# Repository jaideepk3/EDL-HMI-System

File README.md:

# HMI System for Corrosion Monitoring Product WEL-iPEC

This repository contains the development files for a Human Machine Interface (HMI) system designed for use with a corrosion monitoring product (iPEC-Probe). The HMI system includes a user interface with buttons connected to a microcontroller. Due to the unavailability of direct connection with the iPEC Probe, various sensors have been used to simulate data that will be displayed on the LCD screen.

## Files

The repository consists of the following files:

- **Packaging Enclosure CAD**: This folder contains CAD files for the packaging enclosure of the HMI system.

- **Board Files**: This folder contains the PCB design files for the microcontroller board.

- **HMI Code**: This folder contains the complex code that runs the HMI system.

- **Project Report**: This file is a comprehensive documented report of the entire project. It provides detailed information about the development process, implementation, and results. [Download Project Report](https://github.com/jaideepk3/EDL-HMI-System/blob/main/TUES-25_final_report.pdf)

## Project Description

### Aim
The aim of this project is to develop an HMI system that interfaces with the iPEC-Probe corrosion monitoring product. The HMI system will provide a user interface with buttons connected to a microcontroller. To simulate real-time data, sensors have been utilized instead of the actual iPEC Probe.

### Description
The project utilizes a Raspberry Pi Pico microcontroller board as the central controller for the HMI system. The microcontroller board interfaces with various buttons and an LCD screen. The buttons enable user interaction with the LCD screen, while the microcontroller controls the display based on the button inputs.

The HMI system displays real-time measurements obtained from various sensors, including the distance traveled from the scanning start point, rebar depth, rebar size, and other parameters. This provides users with an overview of the concrete structure's condition, enabling informed decision-making. The simulated values from the sensors facilitate comprehensive testing of the HMI system.

## Getting Started

To get started with the HMI system development, follow these steps:

1. Clone this repository to your local machine.
2. Navigate to the respective folders to access the CAD files, board design files, and HMI code.
3. Refer to the documentation provided in the report for further instructions.

## Additional Resources

- **Demo Video**: Watch a breadboard circuit demonstration of the HMI system in action. [Watch Demo Video](https://drive.google.com/file/d/1d6G7GhgJb7exQOc0swpD6kvzHQxaDGIW/view?usp=drivesdk)

- **Final Presentation**: Access the final presentation video for a detailed overview of the project. [View Final Presentation](https://drive.google.com/file/d/1m0dKYORe6IZ8-cWrcGXbmrLrGEMQUf9Z/view?usp=share_link)

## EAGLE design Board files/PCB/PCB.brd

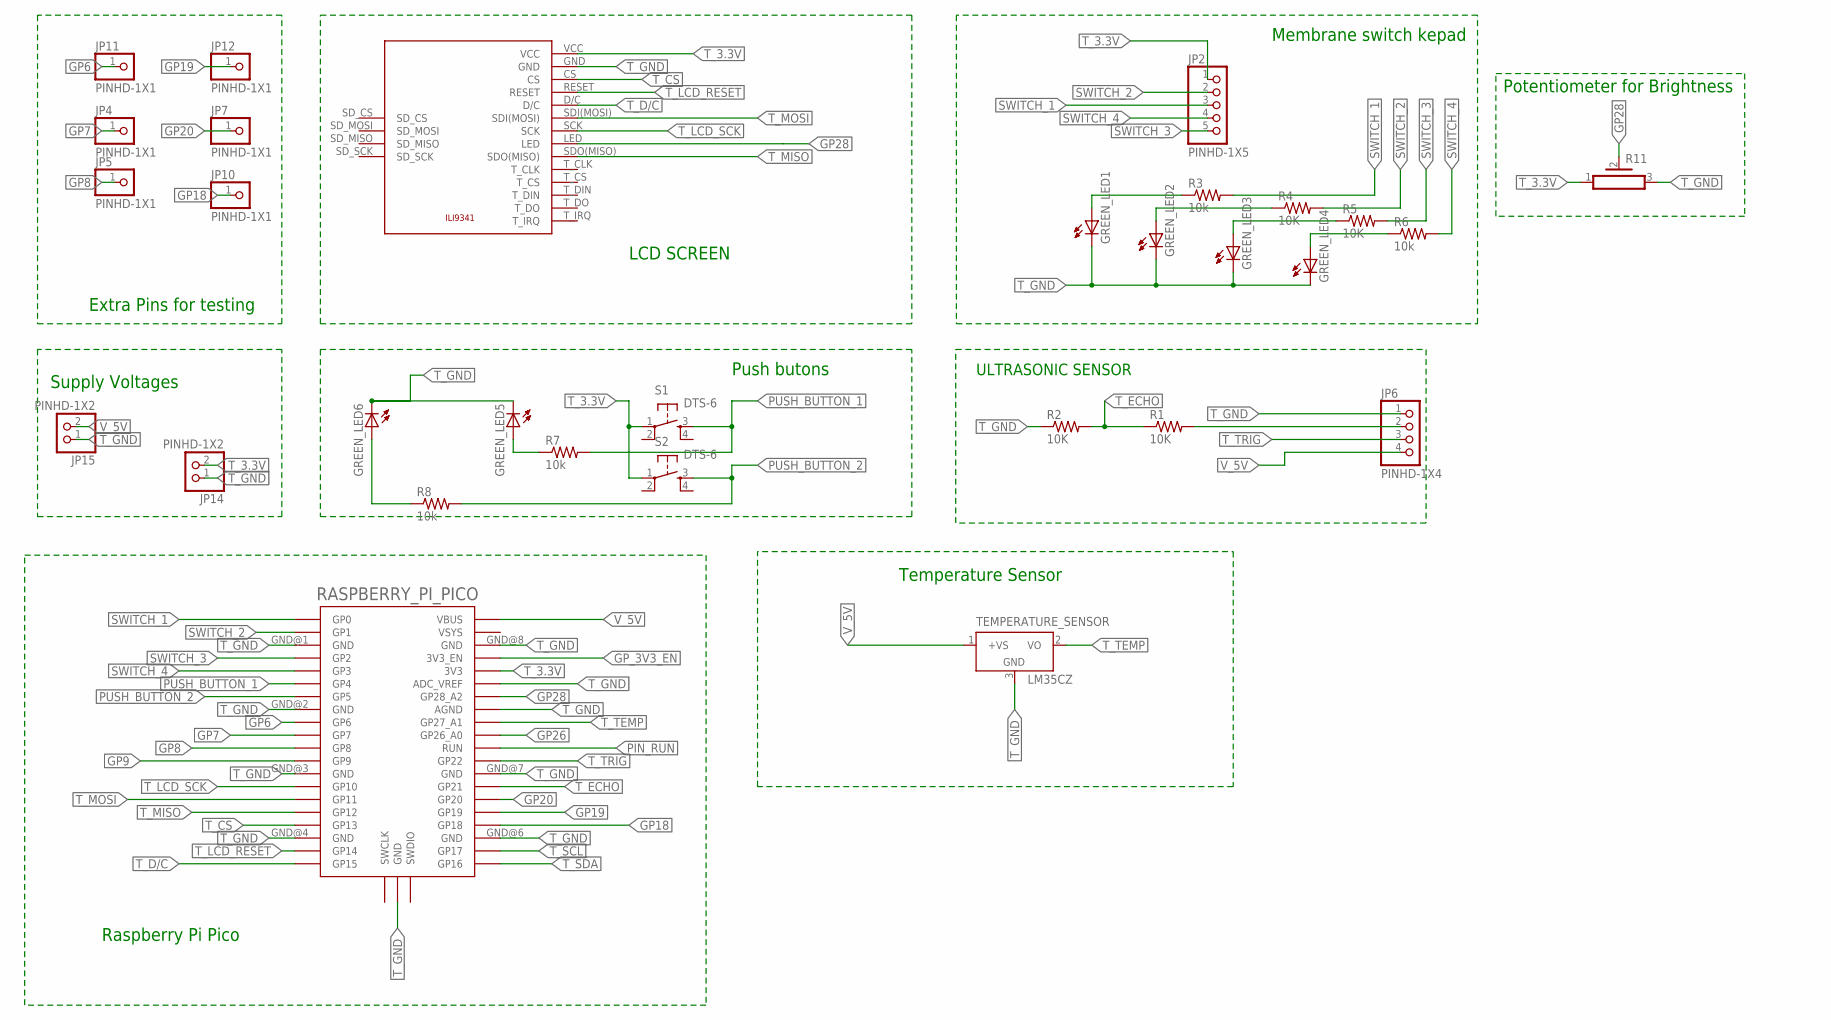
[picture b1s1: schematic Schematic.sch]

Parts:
GREEN_LED1, GREEN_LED2, GREEN_LED3, GREEN_LED4, GREEN_LED5, GREEN_LED6: 3MM_LED_TH; LED3MM
JP2: PINHD-1X5; 1X05
JP4, JP5, JP7, JP10, JP11, JP12: PINHD-1X1; 1X01
JP6: PINHD-1X4; 1X04
JP14, JP15: PINHD-1X2; 1X02
LCD_SCREEN: ILI9341
R1, R2, R4, R5: 10K; 0207/10
R3, R6, R7, R8: 10k; 0207/10
R11: PV36Y
RASPBERRY_PI_PICO: RPI_PICO_IG-TH; RPI_PICO_TH
S1, S2: DTS-6
TEMPERATURE_SENSOR: LM35CZ; TO92

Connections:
GP6: JP11.1, RASPBERRY_PI_PICO.GP6
GP7: JP4.1, RASPBERRY_PI_PICO.GP7
GP8: JP5.1, RASPBERRY_PI_PICO.GP8
GP9: RASPBERRY_PI_PICO.GP9
GP18: JP10.1, RASPBERRY_PI_PICO.GP18
GP19: JP12.1, RASPBERRY_PI_PICO.GP19
GP20: JP7.1, RASPBERRY_PI_PICO.GP20
GP26: RASPBERRY_PI_PICO.GP26_A0
GP28: LCD_SCREEN.LED, R11.2, RASPBERRY_PI_PICO.GP28_A2
GP_3V3_EN: RASPBERRY_PI_PICO.3V3_EN
unnamed: JP6.2, R1.2
unnamed: GREEN_LED4.A, R6.1
unnamed: GREEN_LED3.A, R5.1
unnamed: GREEN_LED2.A, R4.1
unnamed: GREEN_LED1.A, R3.1
unnamed: GREEN_LED5.A, R7.1
unnamed: GREEN_LED6.A, R8.1
PIN_RUN: RASPBERRY_PI_PICO.RUN
PUSH_BUTTON_1: R7.2, RASPBERRY_PI_PICO.GP4, S1.3
PUSH_BUTTON_2: R8.2, RASPBERRY_PI_PICO.GP5, S2.3
SWITCH_1: JP2.3, R3.2, RASPBERRY_PI_PICO.GP0
SWITCH_2: JP2.2, R4.2, RASPBERRY_PI_PICO.GP1
SWITCH_3: JP2.5, R5.2, RASPBERRY_PI_PICO.GP2
SWITCH_4: JP2.4, R6.2, RASPBERRY_PI_PICO.GP3
T_3.3V: JP2.1, JP14.2, LCD_SCREEN.VCC, R11.1, RASPBERRY_PI_PICO.3V3, S1.1, S2.1
T_CS: LCD_SCREEN.CS, RASPBERRY_PI_PICO.GP13
T_D/C: LCD_SCREEN.D/C, RASPBERRY_PI_PICO.GP15
T_ECHO: R1.1, R2.2, RASPBERRY_PI_PICO.GP21
T_GND: GREEN_LED1.K (C), GREEN_LED2.K (C), GREEN_LED3.K (C), GREEN_LED4.K (C), GREEN_LED5.K (C), GREEN_LED6.K (C), JP6.1, JP14.1, JP15.1, LCD_SCREEN.GND, R2.1, R11.3, RASPBERRY_PI_PICO.ADC_VREF, RASPBERRY_PI_PICO.AGND, RASPBERRY_PI_PICO.GND@1 (GND), RASPBERRY_PI_PICO.GND@2 (GND), RASPBERRY_PI_PICO.GND@3 (GND), RASPBERRY_PI_PICO.GND@4 (GND), RASPBERRY_PI_PICO.GND@5 (GND), RASPBERRY_PI_PICO.GND@6 (GND), RASPBERRY_PI_PICO.GND@7 (GND), RASPBERRY_PI_PICO.GND@8 (GND), TEMPERATURE_SENSOR.3 (GND)
T_LCD_RESET: LCD_SCREEN.RESET, RASPBERRY_PI_PICO.GP14
T_LCD_SCK: LCD_SCREEN.SCK, RASPBERRY_PI_PICO.GP10
T_MISO: LCD_SCREEN.SDO(MISO), RASPBERRY_PI_PICO.GP12
T_MOSI: LCD_SCREEN.SDI(MOSI), RASPBERRY_PI_PICO.GP11
T_SCL: RASPBERRY_PI_PICO.GP17
T_SDA: RASPBERRY_PI_PICO.GP16
T_TEMP: RASPBERRY_PI_PICO.GP27_A1, TEMPERATURE_SENSOR.2 (VO)
T_TRIG: JP6.3, RASPBERRY_PI_PICO.GP22
V_5V: JP6.4, JP15.2, RASPBERRY_PI_PICO.VBUS, TEMPERATURE_SENSOR.1 (+VS)

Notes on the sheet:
LCD SCREEN
ULTRASONIC SENSOR
Membrane switch kepad
Push butons
Supply Voltages
Extra Pins for testing
Raspberry Pi Pico
Potentiometer for Brightness
Temperature Sensor

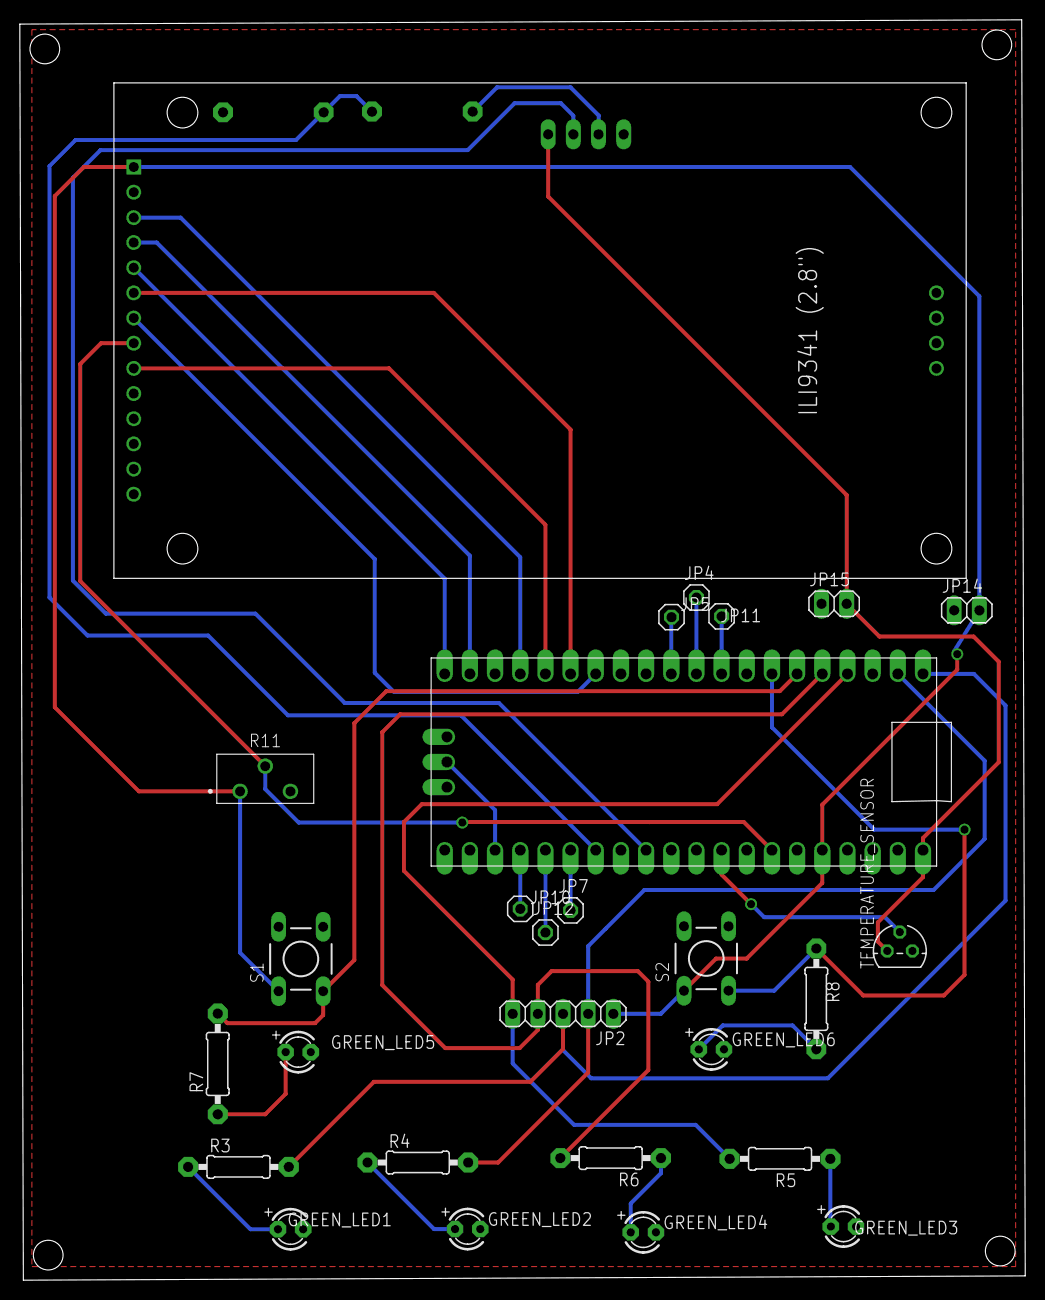
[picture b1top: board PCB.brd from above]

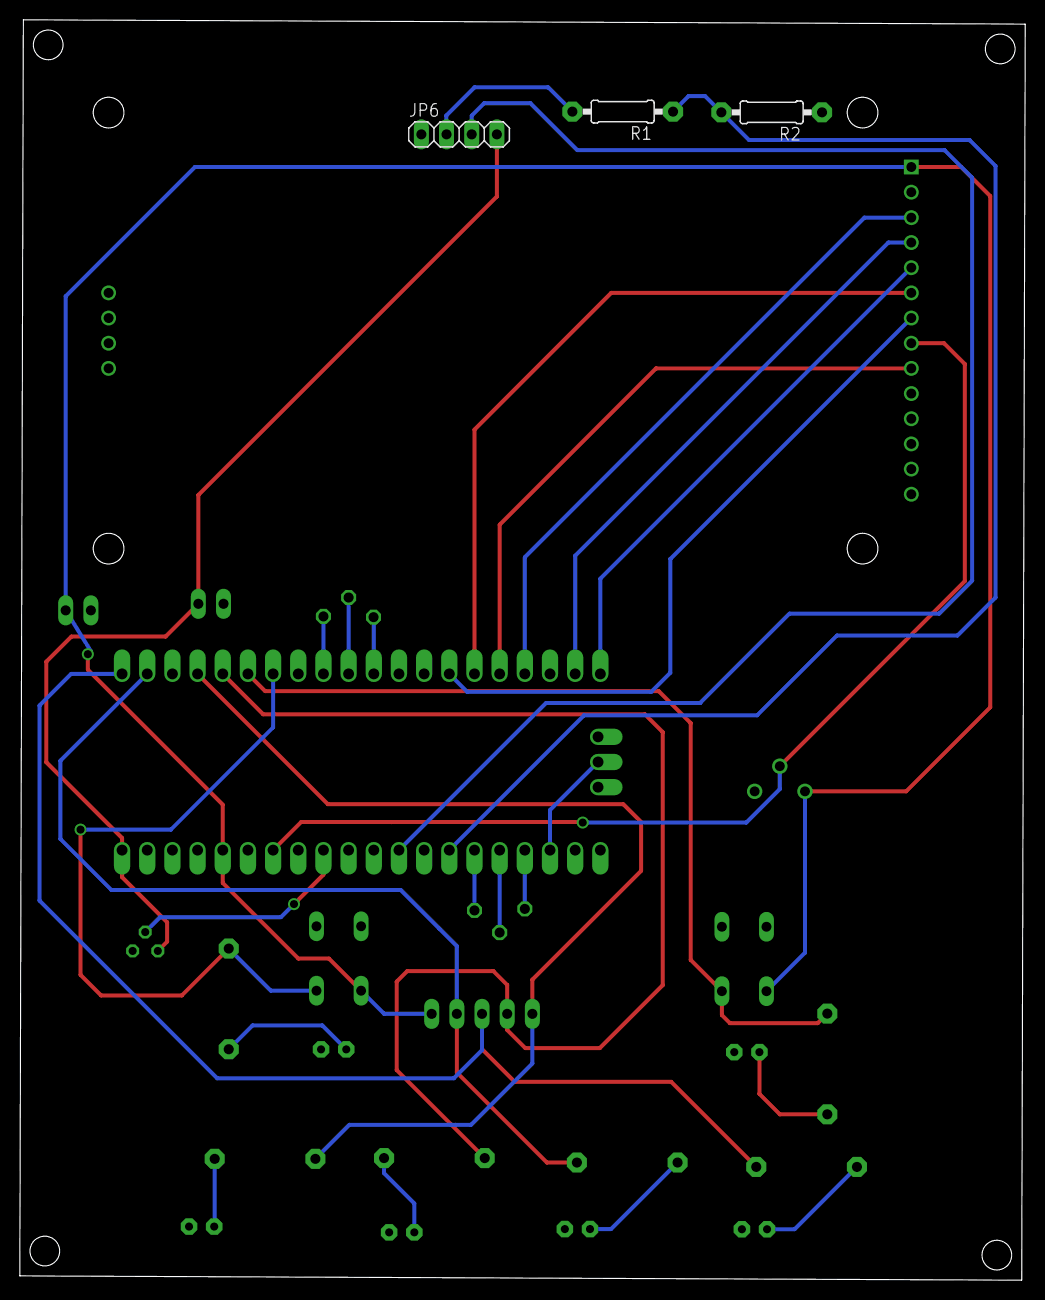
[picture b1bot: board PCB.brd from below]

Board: 2 copper layers, 101.5 x 127.2 mm, 30 parts (3 on the bottom side), 32 nets.

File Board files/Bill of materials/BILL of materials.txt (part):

Partlist exported from C:/Users/seepa/AppData/Local/Temp/Neutron/ElectronFileOutput/8160/sch-04a15b2c-18d9-40eb-af97-f162f59256a9/Schematic v3.sch at 28-04-2023 18:17

Part               Value      Device                Package     Description                                      CATEGORY  DESCRIPTION                            MANUFACTURER MPN   OPERATING_TEMP OPERATING_TEMPERATURE PART_STATUS ROHS_COMPLIANCE ROHS_COMPLIANT SERIES SUB-CATEGORY THERMALLOSS TYPE       
GREEN_LED1         3MM_LED_TH 3MM_LED_TH            LED3MM                                                                                                                                                                                                                                                      
GREEN_LED2         3MM_LED_TH 3MM_LED_TH            LED3MM                                                                                                                                                                                                                                                      
GREEN_LED3         3MM_LED_TH 3MM_LED_TH            LED3MM                                                                                                                                                                                                                                                      
GREEN_LED4         3MM_LED_TH 3MM_LED_TH            LED3MM                                                                                                                                                                                                                                                      
GREEN_LED5         3MM_LED_TH 3MM_LED_TH            LED3MM                                                                                                                                                                                                                                                      
GREEN_LED6         3MM_LED_TH 3MM_LED_TH            LED3MM                                                                                                                                                                                                                                                      
JP2                PINHD-1X5  PINHD-1X5             1X05        PIN HEADER                                       CONNECTOR                                                                                                                                                  PIN-HEADER                          
JP4                PINHD-1X1  PINHD-1X1             1X01        PIN HEADER                                       CONNECTOR                                                                                                                                                  PIN-HEADER                          
JP5                PINHD-1X1  PINHD-1X1             1X01        PIN HEADER                                       CONNECTOR                                                                                                                                                  PIN-HEADER                          
JP6                PINHD-1X4  PINHD-1X4             1X04        PIN HEADER                                       CONNECTOR                                                                                                                                                  PIN-HEADER                          
JP7                PINHD-1X1  PINHD-1X1             1X01        PIN HEADER                                       CONNECTOR                                                                                                                                                  PIN-HEADER                          
JP10               PINHD-1X1  PINHD-1X1             1X01        PIN HEADER                                       CONNECTOR                                                                                                                                                  PIN-HEADER                          
JP11               PINHD-1X1  PINHD-1X1             1X01        PIN HEADER                                       CONNECTOR                                                                                                                                                  PIN-HEADER                          
JP12               PINHD-1X1  PINHD-1X1             1X01        PIN HEADER                                       CONNECTOR                                                                                                                                                  PIN-HEADER                          
JP14               PINHD-1X2  PINHD-1X2             1X02        PIN HEADER                                       CONNECTOR                                                                                                                                                  PIN-HEADER                          
JP15               PINHD-1X2  PINHD-1X2             1X02        PIN HEADER                                       CONNECTOR                                                                                                                                                  PIN-HEADER                          
LCD_SCREEN         ILI9341    ILI9341               ILI9341                                                                                                                                                                                                                                                     
R1                 10K        RESISTOR_1/4W_0207/10 0207/10                                                                                                                                                                                                                                                     
R2                 10K        RESISTOR_1/4W_0207/10 0207/10                                                                                                                                                                                                                                                     
R3                 10k        RESISTOR_1/4W_0207/10 0207/10                                                                                                                                                                                                                                                     
R4                 10K        RESISTOR_1/4W_0207/10 0207/10                                                                                                                                                                                                                                                     
R5                 10K        RESISTOR_1/4W_0207/10 0207/10                                                                                                                                                                                                                                                     
R6                 10k        RESISTOR_1/4W_0207/10 0207/10                                                                                                                                                                                                                                                     
R7                 10k        RESISTOR_1/4W_0207/10 0207/10                                                                                                                                                                                                                                                     
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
